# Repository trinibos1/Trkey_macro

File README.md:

# Trkey Macropad
## Overview

This is a **compact 3×3 macropad** built with **Raspberry Pi Pico / RP2040**, running **CircuitPython/Arduino**. It connects via **USB** using the **Adafruit HID library**, allowing you to assign keyboard shortcuts, media keys, and macros. An **OLED display** shows layer and status information for easy feedback. 
* **OLED Display:** [Amazon Link](https://a.co/d/afDOQYH)
* **PCB Design:** [OSH Park Project](https://oshpark.com/shared_projects/1jOtq57X)
* **Web Key Mapper:** [trinibos1/Trkey\_mapper](https://trinibos1.github.io/TRkey_mapper/)

---
## Update

* UF2 file is old but code is up to date
* wireless trkey macropad has started development
---
## Changelog / Update Log

- **2026-02-14**
  - Added startup boot animation to main Arduino sketch (`arduino/Trkey_macro.ino`) with 3x3 box reveal, `TRKEY` splash, and version text.
  - Added dedicated WebSerial + USB connection guide (`WEBSERIAL_CONNECTION.md`).
  - Improved Arduino firmware compatibility and robustness:
    - HID report ID fixes for keyboard/media reports.
    - Numeric key token support (`"1".."0"`) plus legacy aliases (`"ONE".."ZERO"`).
    - RAM-backed `layers.json` handling when LittleFS is unavailable.
    - Safer JSON fallback behavior and macro ID parsing improvements.
    - USB descriptor naming updates for Trkey product/manufacturer.

## Features

* 3×3 Cherry MX Brown Hyperglide 45g tactile mechanical key matrix
* USB HID support (no Bluetooth)
* OLED display for layer/status feedback
* Tap/Hold functionality for advanced key actions
* Multiple layers for extended shortcut options
* Fast and responsive keypresses
* Simple wiring: switches connect directly to GND
* **All-in-one UF2:** CircuitPython, libraries, and firmware code included

---

## Hardware

| Component       | Details                                                                    |
| --------------- | -------------------------------------------------------------------------- |
| Microcontroller | Raspberry Pi Pico / RP2040                                                 |
| Switches        | 9x Cherry MX Brown Hyperglide 45g tactile                                  |
| Display         | OLED I2C 128x32 ([link](https://a.co/d/afDOQYH))                           |
| PCB             | Custom 3×3 macropad ([link](https://oshpark.com/shared_projects/1jOtq57X)) |
| Power           | USB only                                                                   |

PCB 

---

## Firmware

**UF2 Firmware:**

* `macropad.uf2` — stable, all-in-one with CircuitPython, libraries, and code
* `dev_firmware.uf2` — development version for testing new features

**Key Features:** Tap/Hold, Layers, Media keys

### Arduino IDE firmware (C/C++)

If you want to move from CircuitPython to Arduino IDE, use `arduino/Trkey_macro.ino`.

Startup animation is now included in the main sketch (`arduino/Trkey_macro.ino`).

For beta experiments, you can still use `arduino/Trkey_macro_Beta.ino` (also provided as `arduino/Trkey_macro Beta.ino`).

This sketch keeps the same behavior as `code.py`:
- 3x3 key scanning with debounce + key repeat
- Layer functions: `MO(x)`, `TO(x)`, `TT(x)`, `DF(x)`
- Media keys + keyboard combos + text macros (`MACRO_n`)
- Text macro typing fallback is ASCII-only (`A-Z`, `a-z`, `0-9`, space, newline)
- OLED layer/key UI (with highlighted key and boxed grid)
- Serial command protocol for `LIST`, `GET`, `PUT`, `DEL`, `RELOAD`
- Macros can be defined on any layer; duplicate IDs use the last parsed definition

Required Arduino libraries:
- Adafruit SSD1306
- Adafruit GFX Library
- TinyUSB from the RP2040 board core (`Adafruit_TinyUSB_Arduino`)
- ArduinoJson
- LittleFS (included with RP2040 core)

Recommended board core: **Raspberry Pi Pico/RP2040** (Earle Philhower core).

RP2040 TinyUSB note (important):
- Do **not** call `tusb_init()` in your sketch (the RP2040 Arduino core already initializes TinyUSB).
- Prefer the TinyUSB bundled with the RP2040 core (`Adafruit_TinyUSB_Arduino`).
- If you installed `Documents/Arduino/libraries/Adafruit_TinyUSB_Library`, remove it to avoid library conflicts.

Documentation:
- `WEBSERIAL_CONNECTION.md` — USB CDC/WebSerial command flow, upload handshake, persistence behavior, and troubleshooting.
- `layers.json` in repo root — example keymap/profile format used by firmware and mapper.

---

## Usage

1. **Flash the UF2** (`macropad.uf2` or `dev_firmware.uf2`) onto your Pico — everything is included, no additional setup needed.
2. **Plug in the macropad** — ready to use.
3. **Use your macropad**:

   * Tap switches for primary actions
   * Hold switches for secondary actions or layer switching
   * OLED displays the current layer and status

---

## Companion App (Beta)

This beta feature is implemented in **Arduino firmware** (`arduino/Trkey_macro.ino`) and an optional PC CLI app (`pc_companion/trkey_music_companion.py`).

- The macropad still works fully without the companion app.
- Companion mode adds now-playing OLED metadata and app events.
- You can switch to music layer by name with: `MODE music`.

Quick start:
1. Flash Arduino beta firmware (`arduino/Trkey_macro_Beta.ino`).
1. Flash Arduino firmware (`arduino/Trkey_macro.ino`).
2. Run companion app: `python pc_companion/trkey_music_companion.py --port <PORT>`.
3. In app CLI, type:
   - `music` to load the music layer by name.
   - `np Song|Artist|45|180|Spotify` to update metadata.

Supported companion key tokens (in `layers.json`):
- `APP_PLAY_PAUSE`
- `APP_NEXT`
- `APP_PREV`
- `APP_MUTE`
- `APP_VOL_UP`
- `APP_VOL_DOWN`
- `APP_SEEK_FWD_10`
- `APP_SEEK_BACK_10`

`APP_*` keys emit `APP_EVENT <token>` on serial and media actions also fallback to HID media controls.

## Web-Based Key Mapper

Customize your macropad's key bindings using the **web-based key mapper**:

* Full key remapping: Assign single keys or complex shortcuts to any of the 9 keys
* Multi-layer support: Configure multiple layers for extended functionality
* Macro support: Create macros for complex sequences
* Web Serial API: Communicate directly with your macropad via the browser

**Access the key mapper here:** [trinibos1/micropad\_web](https://github.com/trinibos1/micropad_web)

---

## Contributions

Contributions are welcome to **improve the key library**, including:

* Adding new key mappings or shortcuts
* Optimizing tap/hold behavior
* Enhancing multi-layer support
* Improving key response and stability

Submit issues or pull requests to collaborate.
---
## 🙌 Thanks

Huge thanks to **[Adafruit](https://www.adafruit.com/)** for their amazing hardware and the **CircuitPython** + library ecosystem.  
Without their work, projects like this macropad wouldn’t be possible. 💜
---

## License

MIT License – see [LICENSE](LICENSE) for details.
---
## contact
Email: Trinibos1@proton.me

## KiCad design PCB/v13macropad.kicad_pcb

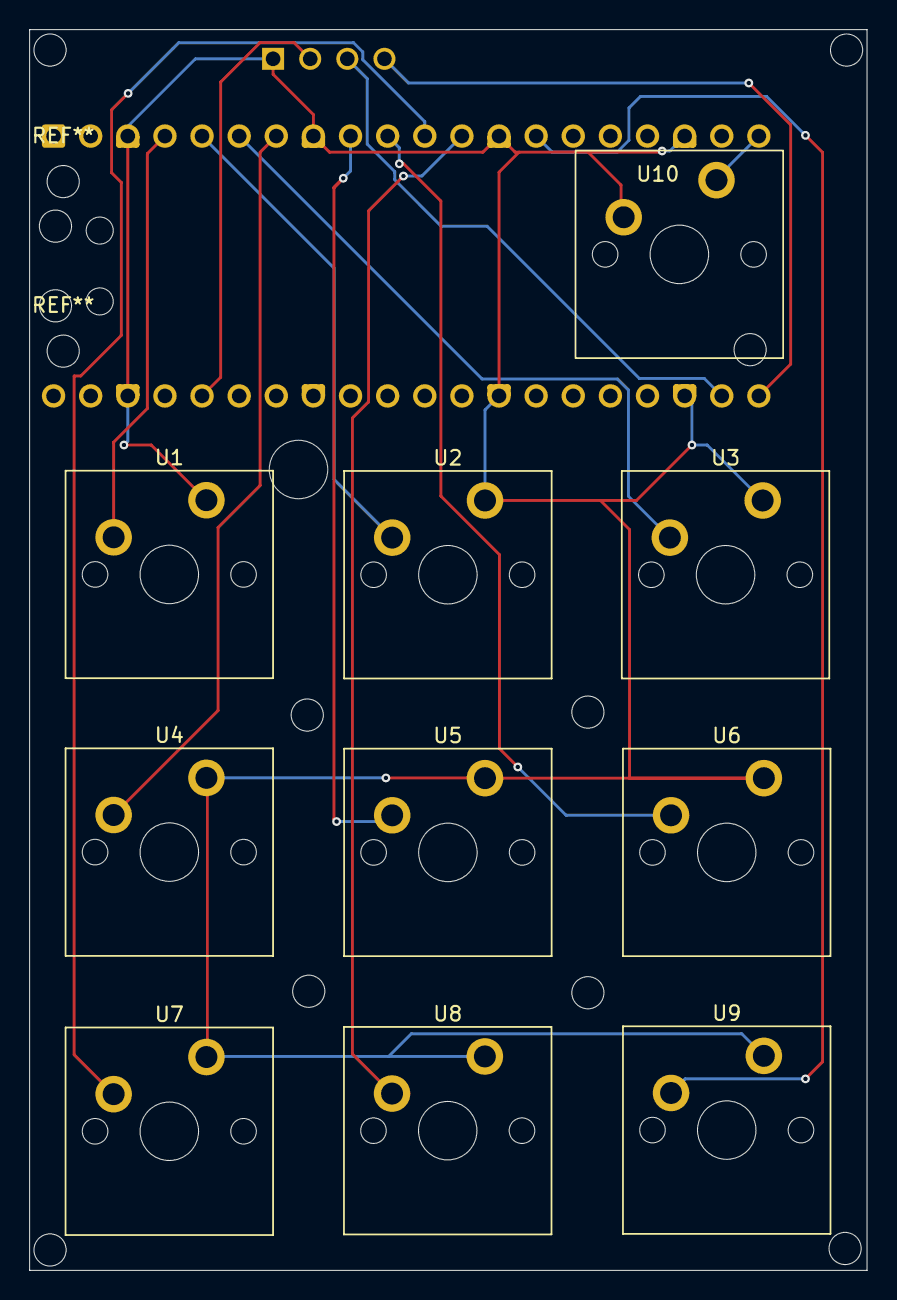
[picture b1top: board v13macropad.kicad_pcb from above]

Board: 2 copper layers, 57.3 x 84.9 mm, 12 parts (1 on the bottom side), 11 nets.

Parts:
A1: RaspberryPi_Pico; RaspberryPi_Pico_Common
U1, U2, U3, U4, U5, U6, U7, U8, U9, U10: MX1A-11NN; SW_Cherry_MX_PCB_1.00u
U11: DM-OLED096-636; MODULE_DM-OLED096-636

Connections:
BAT+: A1.6 (GPIO4), A1.10 (GPIO7), A1.14 (GPIO10), A1.36 (3V3), A1.39 (VSYS), A1.40 (VBUS), U3.1, U6.1, U9.1, U11.2 (VCC_IN)
Earth: A1.3 (GND), A1.8 (GND), A1.13 (GND), A1.18 (GND), A1.23 (GND), A1.28 (GND), A1.38 (GND), U1.2, U2.2, U3.2, U4.2, U5.2, U6.2, U7.2, U8.2, U9.2, U10.1, U11.1 (GND)
unnamed: A1.4 (GPIO2), U1.1
unnamed: A1.5 (GPIO3), U2.1
unnamed: A1.7 (GPIO5), U4.1
unnamed: A1.9 (GPIO6), U5.1
unnamed: A1.11 (GPIO8), U7.1
unnamed: A1.12 (GPIO9), U8.1
unnamed: A1.20 (GPIO15), U10.2
unnamed: A1.21 (GPIO16), U11.4 (SDA)
unnamed: A1.22 (GPIO17), U11.3 (SCL)

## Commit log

2025-08-18 Create my-folder
2025-08-18 Create place holder
2025-08-18 Rename macropadfirmware.uf2 to uf2/macropadfirmware.uf2
2025-08-18 Rename devfirmware.uf2 to uf2/devfirmware.uf2
2025-08-18 Create CASE COMING SOON
2025-08-18 Rename firmware.uf2 to uf2/devfirmware.uf2
2025-09-01 case
2025-09-02 Rename macropad printed parts only.jpg to images/macropad printed parts nly.jpg
2025-09-02 Rename image_2025-09-02_182150833.png to image/pcb.png
2025-09-02 Rename macropad together.jpg to images/macropad together.jpg
2025-09-02 Rename PXL_20250902_222032871.jpg to pcb.jpg
2025-09-02 Rename macropad together.jpg to macropadtogether.jpg
2025-11-22 Update README with new information and corrections
    Added update section and fixed minor text issues.
2025-11-22 Rename case/macropad bottom .stl to case/old/macropad bottom .stl
2025-11-22 Rename macropad bottom .stl to macropad bottom .stl
2025-11-22 Rename case/macropad mid.stl to case/oldcase/macropad mid.stl
2025-11-22 Rename case/macropad top.stl to case/oldcase/macropad top.stl
2025-11-22 Create New case Placeholder
2025-11-22 Update README with new case design date and Discord info
    Updated release date for new case design and added Discord server announcement.
2025-11-22 Fix typo in README regarding Discord server
2025-12-12 Update case design release date in README
2025-12-22 Revise README with code update and feature notes
    Updated README to reflect code changes and upcoming features.
2025-12-24 Update README to reflect code change to Arduino C++
2025-12-26 Add note about V2 trkey macropad development
2026-02-14 Fallback to built-in keymap instead of OLED ERROR state
2026-02-14 Fix CDC command handling and layers.json boot loading
2026-02-14 Fix Arduino layer JSON compatibility and macro parsing
2026-02-14 Avoid ERROR fallback screen by loading safe default layer
2026-02-14 Fix HID report IDs so key presses are sent
2026-02-14 Support RAM-backed layers.json when LittleFS is unavailable
2026-02-14 Accept numeric key tokens in Arduino key map
2026-02-14 Add dedicated WebSerial connection documentation
2026-02-14 Set USB product and serial descriptors to Trkey
2026-02-14 Apply USB Trkey descriptors before core USB init
2026-02-14 Use USBDevice descriptors for Trkey product/manufacturer
2026-02-14 Revert "Set USB product to 'Trkey' and improve WebSerial/layers handling"
2026-02-14 Refresh project docs for USB, WebSerial, and JSON behavior
2026-02-14 Add changelog section to README
2026-02-14 Implement Arduino beta companion mode with music layer command and PC app
2026-02-14 Move companion beta implementation into Trkey_macro_Beta sketches
2026-02-14 Fix text macro typing and improve layers.json persistence path
2026-02-14 Fix JSON API warnings and harden LittleFS PUT persistence
2026-02-14 Improve HID readiness and add serial HID test command
2026-02-14 Remove over-strict HID gating and add serial TYPE test
2026-02-14 Add keyboard report-id fallback and HIDINFO command
2026-02-14 Switch to explicit HID report send with counters for diagnostics
2026-02-14 Fix keyboard report ID usage for HID typing
2026-02-14 Fix TinyUSB keyboard report transmission with report IDs
2026-02-15 Fix layer JSON reload capacity for larger configs
2026-02-15 Retry LittleFS mount during serial commands and reload
2026-02-15 Fix upload EOF handling, FS resilience, and input timing
2026-02-15 Prioritize fresh RAM config and make PUT writes atomic
2026-02-15 Update Trkey_macro.ino
    everything but hid is working
2026-02-15 Update Trkey_macro.ino
    It load the layers.json to ram but not flash, so on reboot it lose the the mapping that was in Layers.json
2026-02-15 Update Trkey_macro.ino
    this should save the layers.json to flash but hasnt been tested yet
2026-02-16 Update Trkey_macro.ino
    Replaced LittleFS with EEPROM storage
    version=2.5.4
2026-03-04 Update trkey_music_companion.py
    buggy as hell, dont use
